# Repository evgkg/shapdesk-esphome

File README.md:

# Shapdesk ESPHome

**English** · [Русский](README.ru.md)

A small add-on that connects a **Shapdesk** standing desk to Home Assistant over Wi-Fi. An ESP32-C3 SuperMini board lives in a little 3D-printed box on the back of the original handset. It presses the handset's buttons for you and reads the desk height from the data the handset sends over UART. In Home Assistant the desk shows up through ESPHome: raise and lower it, send it to a height, recall presets 1–4 and press M.

The buttons on the handset still work as before, and the desk controller's own protections stay in place.

| Handset | Add-on on the back | USB-C for flashing |
|---|---|---|
|  |  |  |

## Contents

- [How it works](#how-it-works)
- [What's where](#whats-where)
- [Hardware](#hardware) · [Board revisions](#board-revisions) · [rev1 issue](#known-issue-rev1-the-desk-moves-down-while-flashing) · [Ordering the PCB](#ordering-the-pcb) · [Parts list](#parts-list)
- [Assembly guide](docs/assembly.md)
- [Firmware](#firmware) · [In Home Assistant](#what-you-get-in-home-assistant) · [Settings](#settings) · [Protection](#protection-against-unwanted-movement) · [First test](#first-test-on-the-desk) · [Tests on a PC](#tests-on-a-pc)

## How it works

The handset's buttons are wired as a matrix: each button connects one of the **T5/T4** lines to one of the **T3** lines. T3, T4 and T5 are three small SOT-23 parts on the handset board, and their legs are handy places to solder to. The add-on has a transistor across each button. When the ESP switches a transistor on, it shorts the button, and the handset can't tell that apart from a finger press.

The handset also keeps sending data on its **RX** line (5 V UART, 9600 8N1): the desk position and what's on the display. The add-on only listens; it never sends anything to the handset.

| Key | Button | GPIO on rev2 | GPIO on rev1 |
|---|---|---:|---:|
| K1 | ▲ up | 5 | 5 |
| K2 | ▼ down | **3** | **6** |
| K3 | preset 1 | 7 | 7 |
| K4 | preset 2 | **0** | **10** |
| K5 | preset 3 | **10** | **0** |
| K6 | preset 4 | 1 | 1 |
| K7 | M | **4** | **3** |
| UART RX | handset data, through a 10k/18k divider | **6** | **4** |
| USB | logs and flashing | 18/19 | 18/19 |

Each GPIO drives an MMBT3904 transistor through a 4.7 kΩ resistor, and a 100 kΩ resistor from base to emitter keeps the transistor off until the GPIO is set up. GPIO2/8/9/20/21 are free. The add-on runs off the handset's 5 V through an ME6211 3.3 V regulator; you can plug in USB at the same time.

## What's where

```
shapdesk.yaml              ESPHome config (settings at the top)
components/shapdesk/       ESPHome component in C++; the main logic doesn't depend on ESPHome
tests/                     PC tests: handset data parsing, height, moving to a height
hardware/pcb/              rev2 board in KiCad 10, Gerber files, make_fab.bat
hardware/enclosure/        enclosure and connector retainer (STL and STEP)
hardware/bom.csv           parts list
docs/assembly.md           step-by-step build
docs/images/               photos and diagrams
```

## Hardware

### Board revisions

| | rev1 | rev2 (this repository) |
|---|---|---|
| Made | at home, single layer with wire jumpers | by a PCB factory, 2 layers, solder mask, silkscreen |
| Keys K1…K7 | GPIO 5, 6, 7, 10, 0, 1, 3 | GPIO 5, 3, 7, 0, 10, 1, 4 |
| UART RX | GPIO4 | GPIO6 |
| In the firmware | `board_revision: "1"` | `board_revision: "2"` |

Only rev2 files are published. rev1 is mentioned here because the firmware still supports it.

> **rev2 hasn't been ordered or tested in hardware yet.** The circuit is the same as on the working rev1, but the board layout and the GPIO assignment are new.

### Known issue (rev1): the desk moves down while flashing

On the ESP32-C3, **GPIO6** has a weak internal pull-up switched on during reset and in the bootloader (ESP32-C3 datasheet, table 2-1, the note about `EFUSE_DIS_PAD_JTAG`). On rev1 that GPIO presses "down". While the chip sits in the bootloader — a few seconds when you flash over USB — the pull-up turns the transistor on and **the desk drives down**. The firmware can't do anything about it, because it isn't running yet.

- **Fixing rev1:** solder a **4.7 kΩ resistor between GPIO6 and GND**. It overpowers the pull-up, so "down" stays released. Until you do, unplug the cable from J1 before flashing, or at least make sure the desk can't hit anything.
- **On rev2** the keys use GPIO 0, 1, 3, 4, 5, 7 and 10, none of which has a pull-up at reset. UART RX moved to GPIO6, where the pull-up doesn't matter. The GPIOs are assigned in the order that keeps the board traces straight. The firmware is set up for rev2 by default (`board_revision: "2"`).

With the wrong revision set, the firmware drives the wrong GPIOs: keys get mixed up and the add-on can't see the height. So check the boot log (see below) before the first test on the desk. The firmware turns off the pull-up on whichever GPIO RX is connected to, so even with the wrong revision that pin can't press a button.

### rev2 board

| Top (ESP32-C3 SuperMini and J1) | Bottom (all the small parts) |
|---|---|
|  |  |

Schematic: [`hardware/pcb/shapdesk_rev2_schematic.pdf`](hardware/pcb/shapdesk_rev2_schematic.pdf). KiCad 10 project: `hardware/pcb/shapdesk_rev2.kicad_pro`.

### Ordering the PCB

`hardware/pcb/shapdesk_rev2_gerbers.zip` can be uploaded as is to any PCB maker (JLCPCB, PCBWay, etc.):

- 2 layers, 1.6 mm thick, 91.2 × 18 mm, any mask colour, HASL finish is fine.
- All SMD parts (0603, 0805, SOT-23) are on the bottom side.
- The thinnest track and the smallest gap are 0.25 mm, vias are 0.8/0.4 mm — standard for any PCB maker.

If you change the board, `hardware/pcb/make_fab.bat` rebuilds the Gerber files and the ZIP (needs KiCad 10).

### Parts list

Full list with board references: [`hardware/bom.csv`](hardware/bom.csv).

| Qty | Part | Package | Where |
|---:|---|---|---|
| 1 | ESP32-C3 SuperMini (soldered on the pin headers it comes with) | module | U1 |
| 1 | ME6211C33M5G-N, 3.3 V regulator | SOT-23-5 | U2 |
| 2 | 10 µF ceramic capacitor, 10 V or more | 0805 | C1, C2 |
| 7 | MMBT3904 NPN transistor | SOT-23 | Q1–Q7 |
| 7 | 100 kΩ | 0603 | R1–R7 |
| 7 | 4.7 kΩ | 0603 | R8–R14 |
| 1 | 10 kΩ | 0603 | R15 |
| 1 | 18 kΩ | 0603 | R16 |
| 1 | right-angle pin header 2×5, 2.54 mm | through-hole | J1 |
| 1 + 9 | Dupont 2×5 female housing and crimp contacts | 2.54 mm | cable |
| 9 | thin stranded wire | | cable |
| 3 + 3 | heat-set insert **M2 × 2.5 × 3.2** and **M2 × 8** button-head hex screw (ISO 7380) | | board into the enclosure |
| 2 + 2 | heat-set insert **M3 × 4 × 4** and **M3 × 6** button-head hex screw (ISO 7380) | | enclosure onto the handset |
| 1 + 1 | printed enclosure and connector retainer | FDM | `hardware/enclosure/` |

### 3D-printed parts

`hardware/enclosure/` has STL files for printing and STEP files in case you want to change something:

- `shapdesk_enclosure` — the box, 132 × 25.5 × 14.9 mm. The M2 inserts for the board go into its three standoffs. The two holes in the flange (Ø3.4 mm) take the M3 screws that hold it on the handset.
- `shapdesk_connector_retainer` — a spacer between the Dupont plug and the enclosure wall, so the plug can't work its way off J1.

### Wiring to the handset

Nine wires go from J1 to the handset board: GND, RX and 5 V to the pads at the board edge, and the other six to the legs of T3, T4 and T5, two per part.

The whole build, step by step, is in **[docs/assembly.md](docs/assembly.md)**.

## Firmware

The firmware is ESPHome (`esp-idf` framework) with the logic in its own C++ component. It talks to Home Assistant over the encrypted ESPHome API and is found on the network automatically (mDNS). It can be updated over Wi-Fi and starts a backup access point if your Wi-Fi isn't reachable. No MQTT needed. The code that reads the handset and drives the desk to a height doesn't depend on ESPHome and is covered by tests that run on a PC. The ESPHome version is pinned in `requirements.txt`.

### Install and flash

In PowerShell, in the project folder:

```powershell
python -m venv .venv
.\.venv\Scripts\python -m pip install -r requirements.txt
Copy-Item secrets.example.yaml secrets.yaml
```

Put your Wi-Fi network, a password for over-the-air updates, a password for the backup access point and your own API encryption key into `secrets.yaml`. The template has example values that everyone can see, so replace all of them. To generate a key, check the config and build:

```powershell
.\.venv\Scripts\python -c "import secrets,base64; print(base64.b64encode(secrets.token_bytes(32)).decode())"
.\.venv\Scripts\esphome config shapdesk.yaml
.\.venv\Scripts\esphome compile shapdesk.yaml
```

> **Don't forget `board_revision`** at the top of `shapdesk.yaml`: `"2"` (the default) for the factory board from this repository, `"1"` for a home-made rev1.

The first flash goes over USB (use your own COM port):

```powershell
.\.venv\Scripts\esphome upload shapdesk.yaml --device COM3
.\.venv\Scripts\esphome logs shapdesk.yaml --device COM3
```

On boot the log shows the revision and the GPIOs, for example `Board rev2: K1..K7 = GPIO5/3/7/0/10/1/4, UART RX = GPIO6`.

After that you can update over Wi-Fi:

```powershell
.\.venv\Scripts\esphome upload shapdesk.yaml --device shapdesk.local
```

If `shapdesk.local` can't be found, use the IP address. If the add-on can't join your Wi-Fi, it starts its own access point, `Shapdesk Fallback` (password from `secrets.yaml`): connect to it and pick your network. Before an over-the-air update the add-on releases all buttons. If you ever need to put the ESP into the bootloader by hand, use the BOOT and RESET buttons on the SuperMini.

In Home Assistant, open *Settings → Devices & services*. The add-on shows up there as a discovered ESPHome device; add it and enter the encryption key. If it doesn't show up, add the ESPHome integration by hand with the IP address and port 6053.

### What you get in Home Assistant

The entity names in `shapdesk.yaml` are in Russian; rename them however you like.

- **Высота стола** (desk height) — the current height in centimetres. It's empty while the add-on doesn't know the height yet, and for a short while after you press a preset, because the handset then shows the preset's height instead of the real one.
- **Стол** (desk) — the ↑ and ↓ arrows raise and lower the desk, ■ stops it. The desk keeps moving until you stop it, for 20 seconds at most (`max_hold_ms`). Open the card and there's also a slider in percent: 0 % is the lowest height, 100 % the highest, anything in between is the matching height. At 0 % and 100 % the slider works the same as the ↓ and ↑ arrows.
- **Целевая высота** (target height) — set a height in centimetres and the desk goes up or down to it.
- **Пресет 1–4** and **M** — the same as pressing those buttons on the handset.
- **Стоп** (stop) — lets go of whatever button the add-on is holding and cancels a move to the target height. It doesn't stop a preset move: the desk goes to a preset on its own, nothing is holding a button.
- **Стол движется** (desk moving) and **Связь с пультом** (handset link) — whether the desk is moving right now and whether data is coming from the handset.
- Diagnostics: the height shown on the handset, the position in the handset's own units (hidden by default), how much handset data was accepted and rejected, Wi-Fi signal and uptime.

For automations there's an action, `esphome.shapdesk_press_key`: it presses key `key` (1–7, see the table above) and holds it for `duration_ms` milliseconds, for example `{key: 7, duration_ms: 300}`. The exact action name depends on what the device is called in HA. If the parameters are wrong, nothing is pressed and the reason goes to the log.

### Settings

All settings are in the `substitutions` block at the top of `shapdesk.yaml`.

| Setting | Default | What it does |
|---|---:|---|
| `board_revision` | 2 | Board revision: 1 = home-made rev1, 2 = factory rev2 |
| `k3_name`…`k6_name` | Пресет 1…4 | Names of the preset buttons; check which preset is which on your handset |
| `max_hold_ms` | 20000 | The longest "up", "down" and M can be held, ms (1…120000) |
| `pulse_ms` | 300 | Length of a short press, ms (1…500) |
| `start_timeout_ms` | 3000 | How long to wait for the desk to start moving, ms (1…30000) |
| `min_height`, `max_height` | 66, 131 | Lowest and highest height the add-on will drive to, cm (50…150) |
| `tolerance` | 1 | How close to the target counts as arrived, cm (0…5) |
| `stop_offset` | 1 | How far before the target to let go of the button, cm (0…5) |
| `adapt_offset` | true | Tune `stop_offset` automatically |

Why `stop_offset` exists: when the button is let go, the desk keeps moving a little. So to stop exactly at the target, the button has to be let go a bit early. With `adapt_offset` on, after every move the firmware checks how far the desk coasted and nudges `stop_offset` towards it: new value = 0.75 × old + 0.25 × this time's coast (kept within 0…5 cm). Up and down are tracked separately and start again from `stop_offset` after a reboot. Moves where something went wrong (handset data dropped out, the desk went the wrong way, it coasted more than 5 cm) are left out.

### Protection against unwanted movement

What the firmware does so the desk doesn't move by itself:

- **Nothing is pressed on power-up or reboot.** The first thing the firmware does on boot is release every button, before it even joins Wi-Fi. Before the firmware starts, resistors on the board keep the transistors off.
- **Only one button at a time**, with at least 50 ms between presses. If a command to press another button arrives while one is held, the add-on lets go of everything and ignores that command — just send it again.
- **No button is held longer than allowed.** A separate hardware timer watches this, so the button is released even if the main program hangs or is busy. Presets are held for at most 500 ms; "up", "down" and M for at most `max_hold_ms`. Sending the same command again doesn't extend the time.
- **Moving to a height** only starts if the add-on knows the current height for sure. The desk is stopped if the handset goes quiet for more than half a second, the desk moves the wrong way, it doesn't start within `start_timeout_ms`, it reaches a height limit, or the connection to Home Assistant or Wi-Fi drops.
- **Without handset data** you can only move the desk up and down by hand, within `max_hold_ms`. Sending it to a height isn't possible.
- **The desk won't go past `min_height` and `max_height`**, but it can always move back away from a limit.

What the firmware can't do:

- "Stop" only releases buttons the add-on pressed itself. If someone is holding a button on the handset, it can't do anything about it. And if a short preset press made the handset drive the desk to the preset on its own, "Stop" won't stop that — stop it from the handset.
- A burnt-out transistor or a completely frozen ESP is beyond what software can protect against. Always keep the handset within reach.

### First test on the desk

1. Before the first move, use a scope or logic analyser to check that the add-on presses nothing on power-up, reboot and Wi-Fi reconnect, and that a press ends on its own when the time runs out. Check that the handset buttons work as before and that Home Assistant shows the height.
2. Press M briefly (300 ms). Then "up" and "down", 300 ms each, one at a time with a pause in between. Check that the button is released by "Stop", by losing Wi-Fi or Home Assistant, when the time runs out and before an over-the-air update.
3. With the desk standing still, check that the height in Home Assistant matches the handset display. Recall a preset: the preset height the handset flashes on its display must not end up in *Высота стола*.
4. Clear the space above and below the desk and set a height 2–3 cm above or below the current one. Note how long the desk takes to start (the handset wakes up first) and how far it coasts; adjust `start_timeout_ms` and `stop_offset` if needed. Try both directions and the height limits with a hand on the handset.
5. Work out which preset is on which button and name them in `k3_name`…`k6_name`. There's no need to hold preset buttons for long.

### Tests on a PC

You need a C++20 compiler, CMake and Ninja:

```powershell
cmake -S . -B build/host -G Ninja
cmake --build build/host
ctest --test-dir build/host --output-on-failure
```

The tests cover parsing the handset data, checksums, working out the height, rejecting broken data and the counters, and they run moves to a height against a simulated desk. On Windows without a C++ compiler you can `pip install ziglang` and point CMake's `CMAKE_CXX_COMPILER` at `zig.exe`, with `CMAKE_CXX_COMPILER_ARG1=c++`.

## License

[MIT](LICENSE)

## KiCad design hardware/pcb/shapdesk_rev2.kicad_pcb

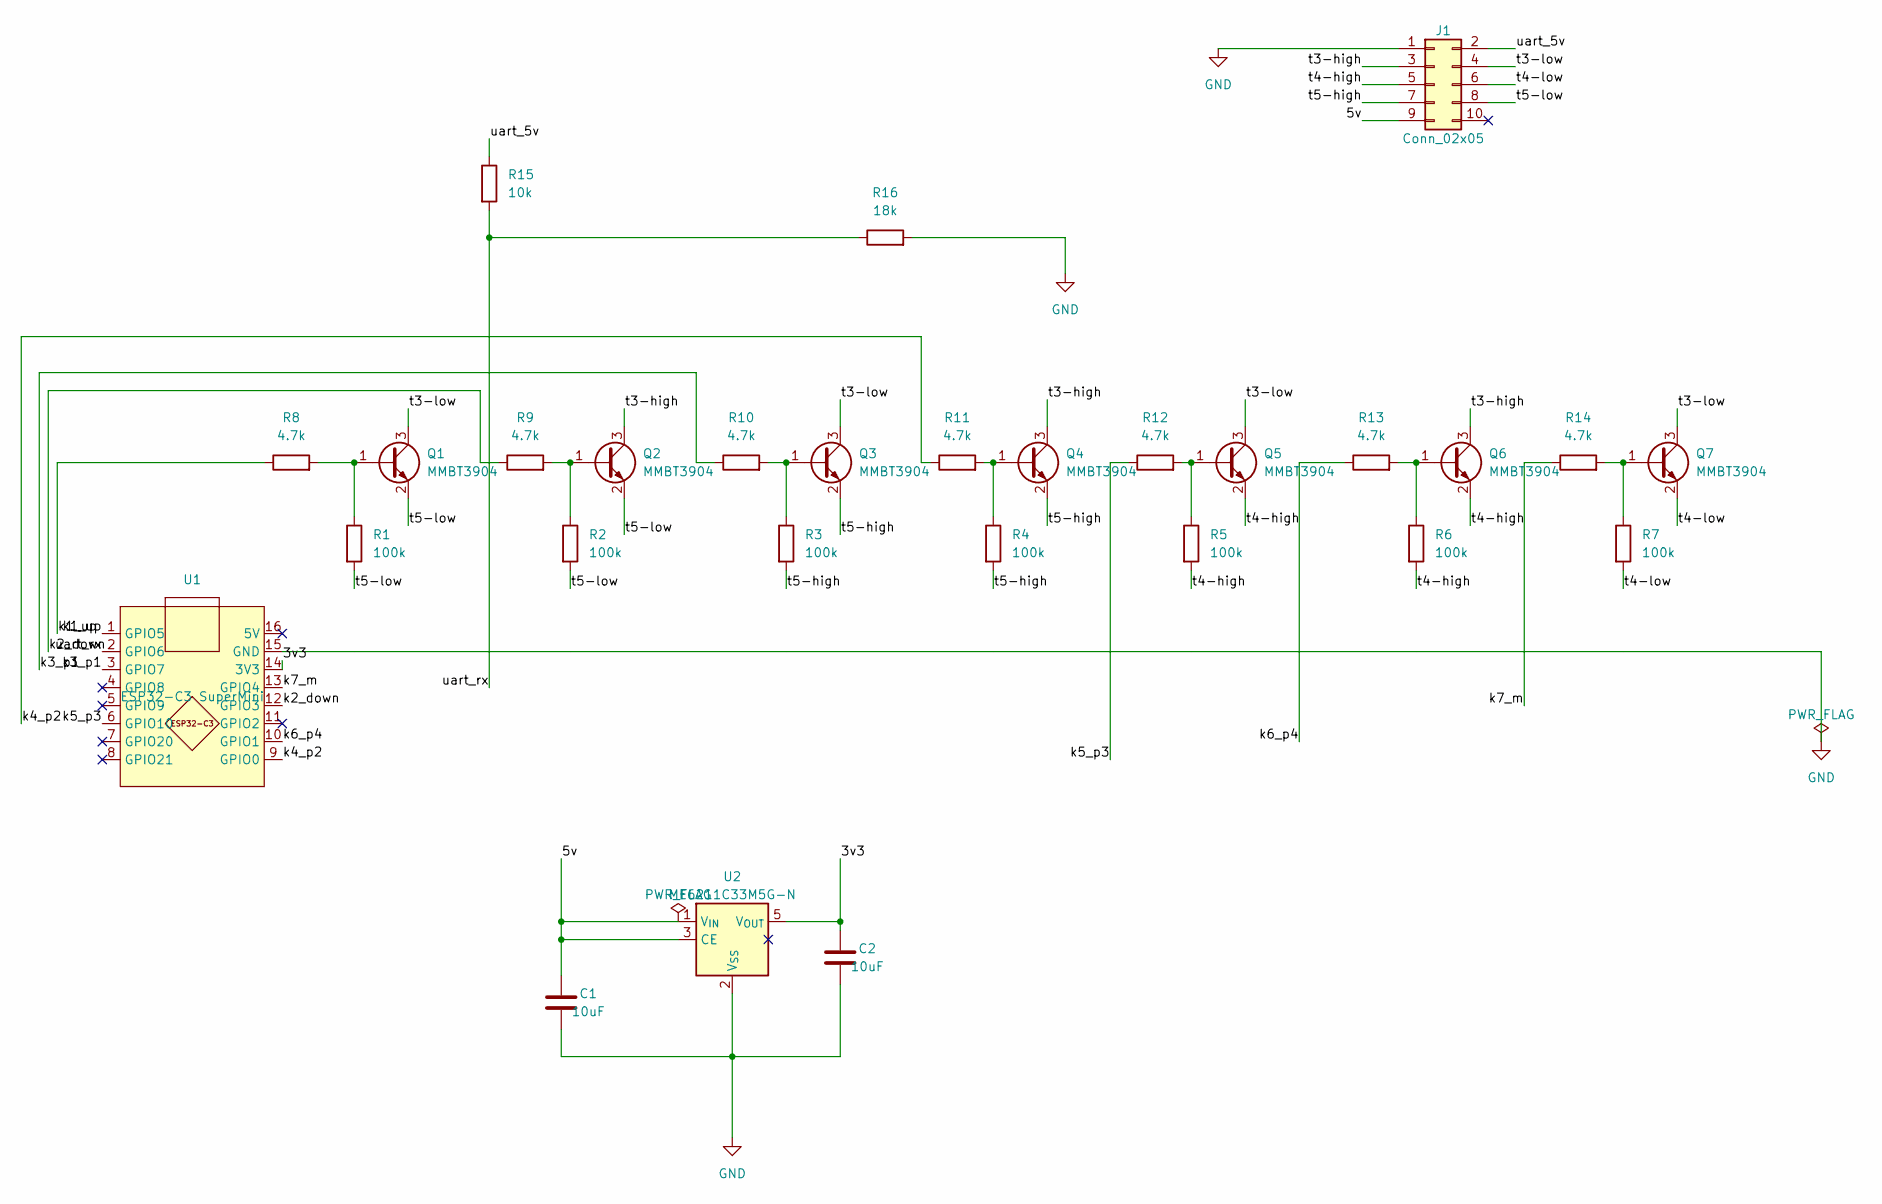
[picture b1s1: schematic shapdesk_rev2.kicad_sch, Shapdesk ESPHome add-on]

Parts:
C1, C2: 10uF; C_0805_2012Metric
J1: Conn_02x05; PinHeader_2x05_P2.54mm_Horizontal
Q1, Q2, Q3, Q4, Q5, Q6, Q7: MMBT3904; SOT-23_Handsoldering
R1, R2, R3, R4, R5, R6, R7: 100k; R_0603_1608Metric
R8, R9, R10, R11, R12, R13, R14: 4.7k; R_0603_1608Metric
R15: 10k; R_0603_1608Metric
R16: 18k; R_0603_1608Metric
U1: ESP32-C3 SuperMini; ESP32-C3_SuperMini_2x08
U2: ME6211C33M5G-N; SOT-23-5

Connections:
/3v3: C2.1, U1.14 (3V3), U2.5 (V_{OUT})
/5v: C1.1, J1.9, U2.1 (V_{IN}), U2.3 (CE)
/k1_up: R8.1, U1.1 (GPIO5)
/k2_down: R9.1, U1.12 (GPIO3)
/k3_p1: R10.1, U1.3 (GPIO7)
/k4_p2: R11.1, U1.9 (GPIO0)
/k5_p3: R12.1, U1.6 (GPIO10)
/k6_p4: R13.1, U1.10 (GPIO1)
/k7_m: R14.1, U1.13 (GPIO4)
/t3-high: J1.3, Q2.3 (C), Q4.3 (C), Q6.3 (C)
/t3-low: J1.4, Q1.3 (C), Q3.3 (C), Q5.3 (C), Q7.3 (C)
/t4-high: J1.5, Q5.2 (B), Q6.2 (B), R5.2, R6.2
/t4-low: J1.6, Q7.2 (B), R7.2
/t5-high: J1.7, Q3.2 (B), Q4.2 (B), R3.2, R4.2
/t5-low: J1.8, Q1.2 (B), Q2.2 (B), R1.2, R2.2
/uart_5v: J1.2, R15.1
/uart_rx: R15.2, R16.1, U1.2 (GPIO6)
GND: C1.2, C2.2, J1.1, R16.2, U1.15 (GND), U2.2 (V_{SS})
unnamed: Q1.1 (E), R1.1, R8.2
unnamed: Q2.1 (E), R2.1, R9.2
unnamed: Q3.1 (E), R3.1, R10.2
unnamed: Q4.1 (E), R4.1, R11.2
unnamed: Q5.1 (E), R5.1, R12.2
unnamed: Q6.1 (E), R6.1, R13.2
unnamed: Q7.1 (E), R7.1, R14.2

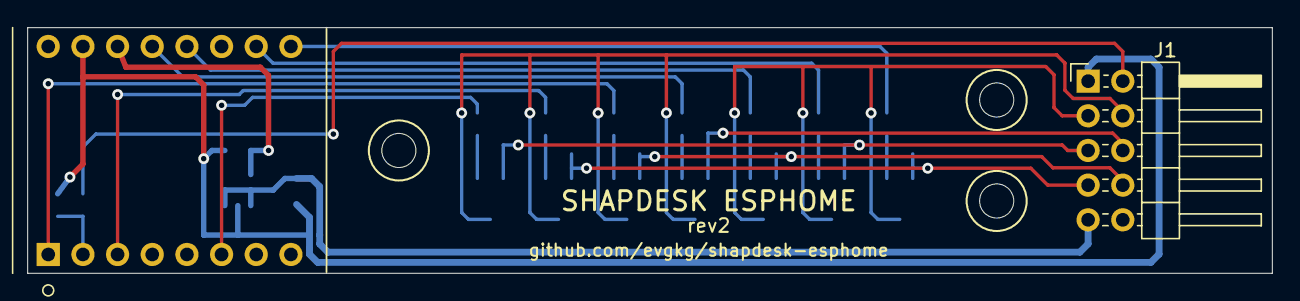
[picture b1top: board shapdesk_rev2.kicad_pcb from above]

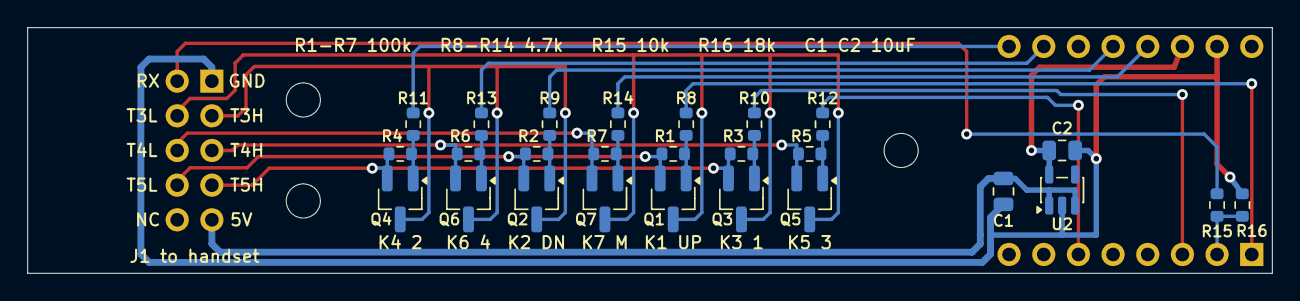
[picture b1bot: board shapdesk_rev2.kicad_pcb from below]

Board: 2 copper layers, 91.2 x 18.0 mm, 31 parts (26 on the bottom side), 25 nets.

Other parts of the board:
H1, H2, H3: M2; MountingHole_2.5mm_M2

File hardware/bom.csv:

Group,Reference,Qty,Value / Part,Package,Notes
Board,PCB,1,shapdesk_rev2 (2 layers 1.6 mm),91.2 x 18 mm,Gerbers: hardware/pcb/shapdesk_rev2_gerbers.zip
Board,U1,1,ESP32-C3 SuperMini,module 2x8 pins 2.54 mm,Soldered on the top side on the 1x8 pin headers supplied with it
Board,U2,1,ME6211C33M5G-N,SOT-23-5,3.3 V LDO from the handset 5 V
Board,"C1, C2",2,10 uF ceramic (>=10 V),0805,LDO input / output
Board,Q1-Q7,7,MMBT3904,SOT-23,NPN key per button
Board,R1-R7,7,100 k,0603,Base-emitter pull-down (keeps keys off during reset)
Board,R8-R14,7,4.7 k,0603,Base series resistor
Board,R15,1,10 k,0603,UART divider (desk 5 V -> 3.2 V)
Board,R16,1,18 k,0603,UART divider
Board,J1,1,Pin header 2x5 right angle,2.54 mm THT,Cable connector
Cable,,1,Dupont housing 2x5 female,2.54 mm,
Cable,,9,Dupont female crimp terminal,2.54 mm,Pin 10 is not used
Cable,,9,Thin stranded wire,,From J1 to the handset PCB (length to suit)
Mechanics,,1,Enclosure,3D print,hardware/enclosure/shapdesk_enclosure.stl
Mechanics,,1,Connector retainer,3D print,hardware/enclosure/shapdesk_connector_retainer.stl
Mechanics,,3,Heat-set insert M2 x 2.5 x 3.2,,Board mounting (melted into the enclosure)
Mechanics,,3,Screw M2 x 8 button head hex socket (ISO 7380),,Board to enclosure
Mechanics,,2,Heat-set insert M3 x 4 x 4,,Melted into the stock handset back shell
Mechanics,,2,Screw M3 x 6 button head hex socket (ISO 7380),,Enclosure to handset
